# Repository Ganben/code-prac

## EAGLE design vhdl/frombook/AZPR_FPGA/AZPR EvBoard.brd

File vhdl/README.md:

## Usage
The env confirmation:
[Source: iverilog wiki](https://iverilog.fandom.com/wiki/Getting_Started)

```
% iverilog -o hello hello.v
% vvp hello
```

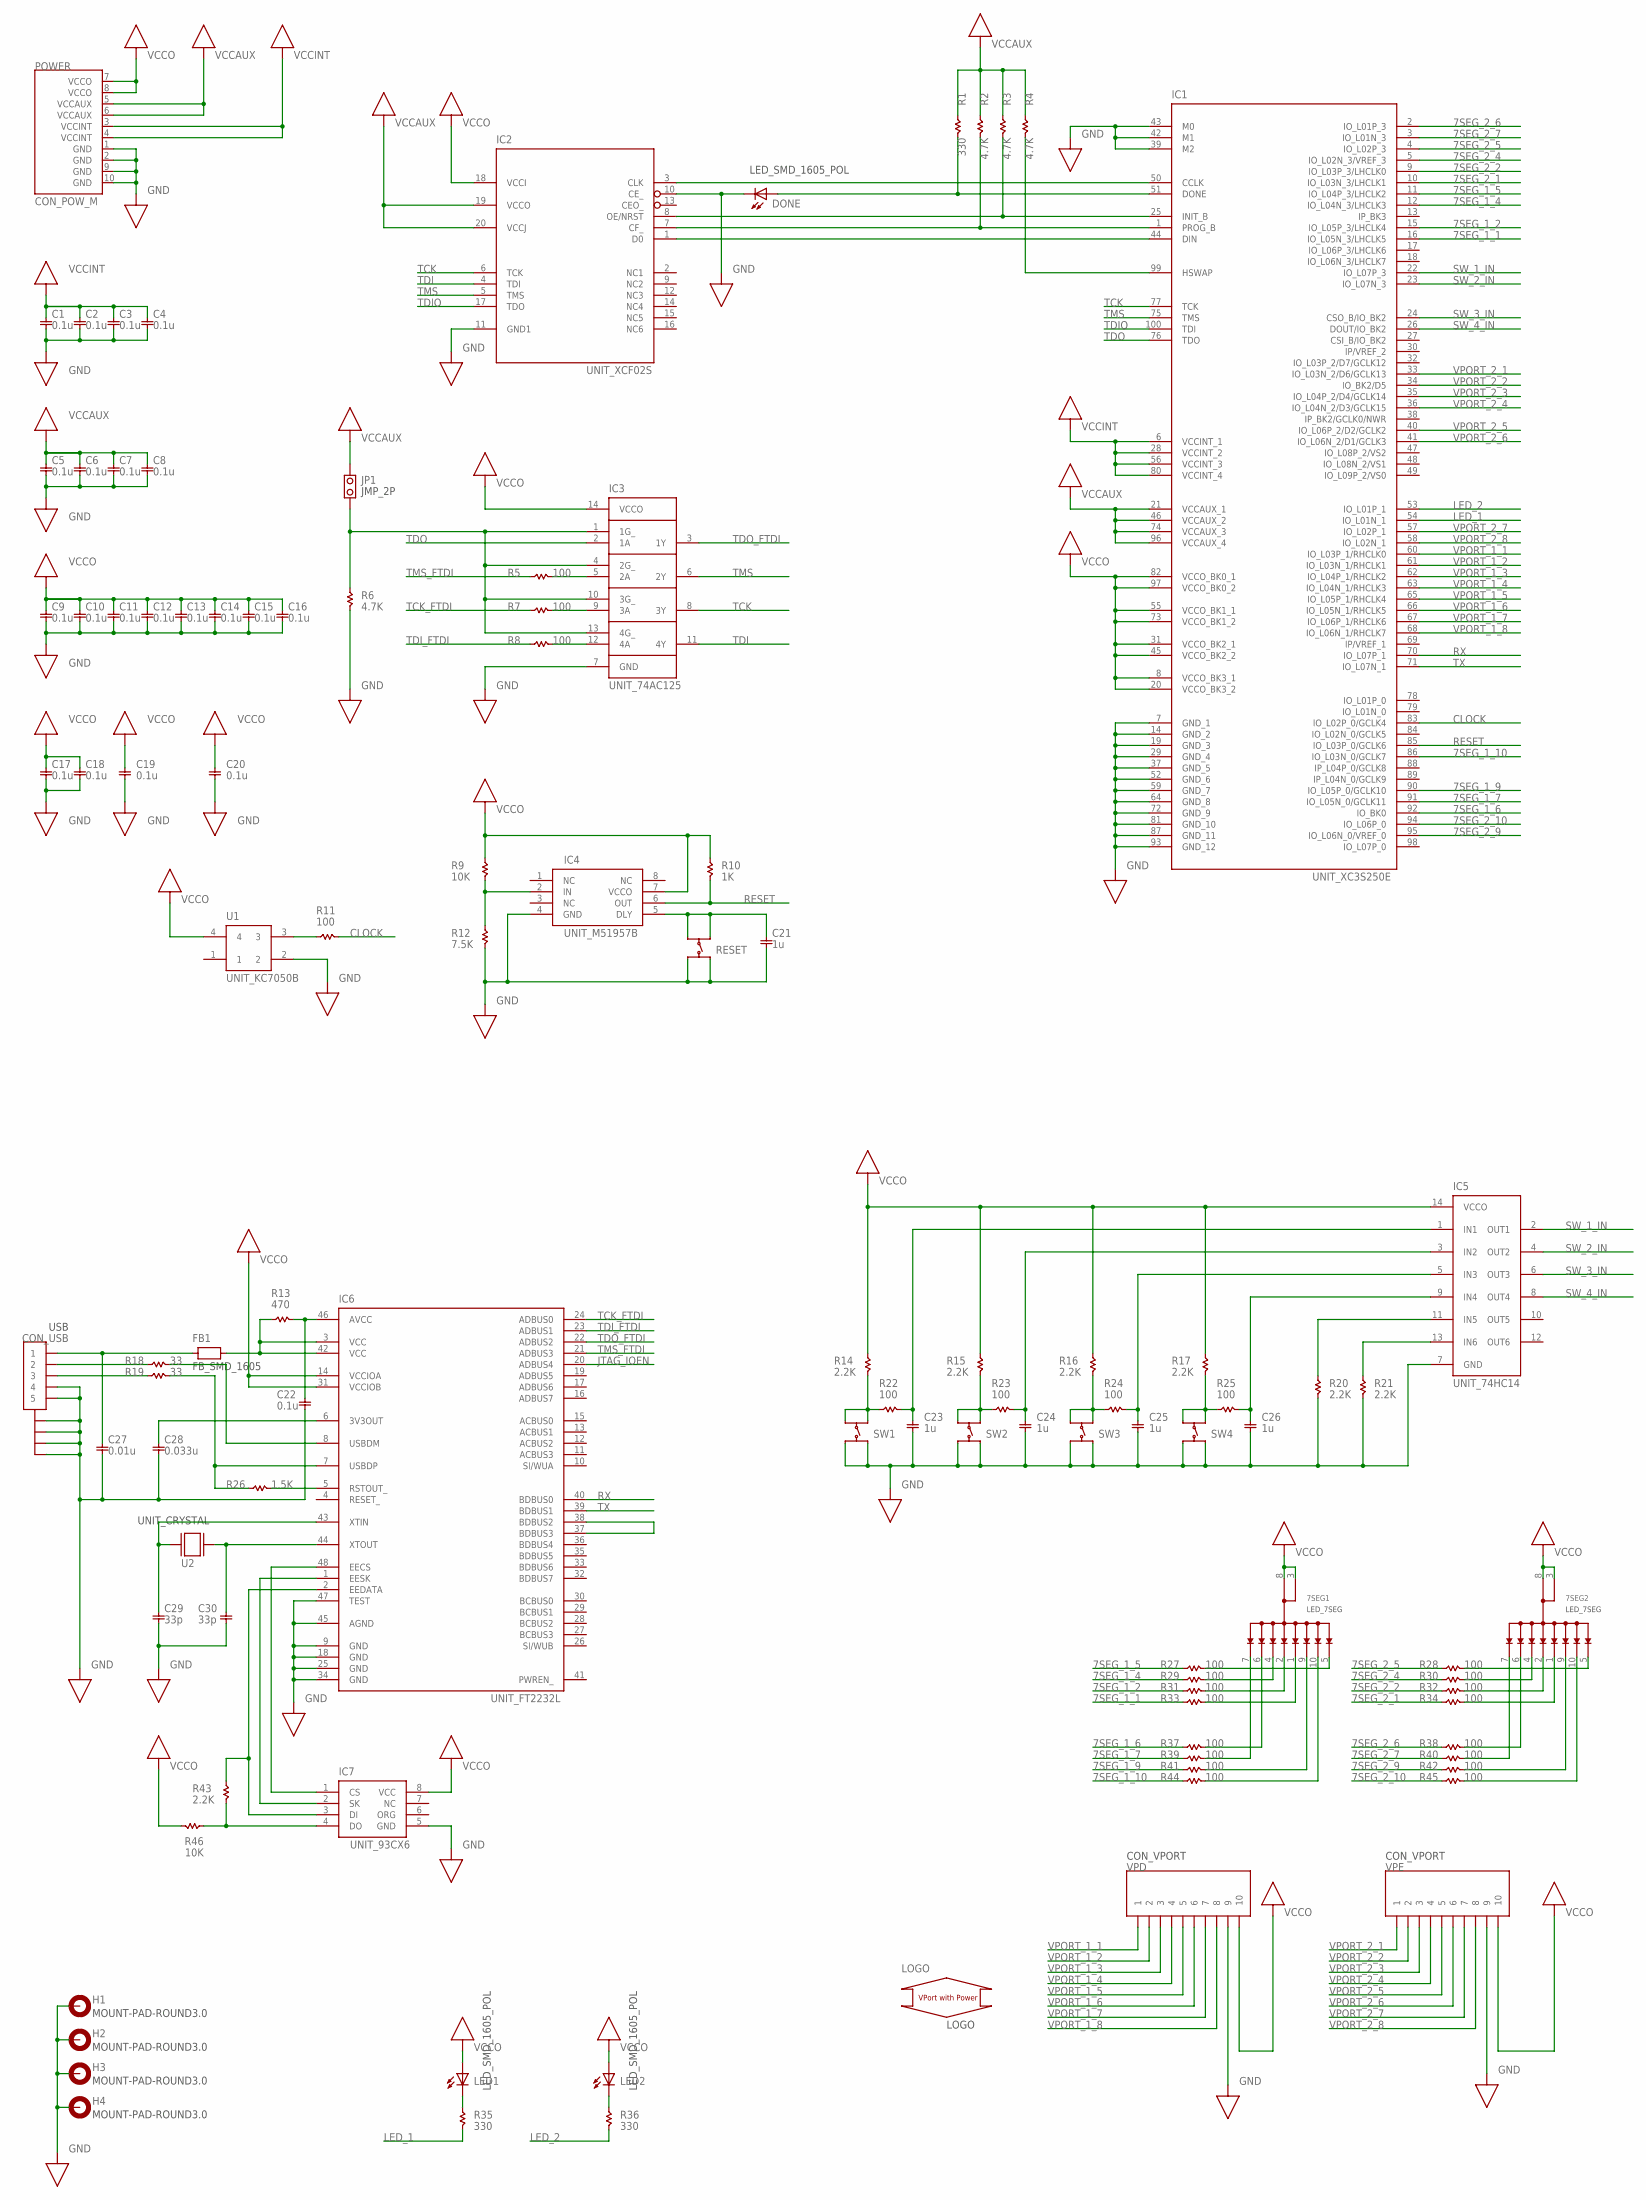
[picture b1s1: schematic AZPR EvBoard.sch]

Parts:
7SEG1, 7SEG2: LED_7SEG; SMD_LED_7SEG
C1, C2, C3, C4: 0.1u; SMDPAD_1605_04INCH
C5, C6, C7, C8: 0.1u; SMDPAD_1605_03INCH
C9, C10, C11, C12, C13, C14, C15, C16, C17: 0.1u; SMDPAD_1605_02INCH
C18, C19, C20, C22: 0.1u; SMD_1605
C21, C23, C24, C25, C26: 1u; SMD_1605
C27: 0.01u; SMD_1605
C28: 0.033u; SMD_1605
C29, C30: 33p; SMD_1605
DONE: LED_SMD_1605_POL; SMD_1605_POL
FB1: FB_SMD_1605; SMD_1605
H1, H2, H3, H4: MOUNT-PAD-ROUND3.0; HOLE_32
IC1: UNIT_XC3S250E; SMD_VQ100
IC2: UNIT_XCF02S; SMD_VO20C
IC3: UNIT_74AC125; SMD_SOP14
IC4: UNIT_M51957B; SMD_SOP8
IC5: UNIT_74HC14; SMD_SOP14
IC6: UNIT_FT2232L; SMD_LQFP48
IC7: UNIT_93CX6; SMD_SOP8
JP1: JMP_2P; PAD_JMP_2P
LED1, LED2: LED_SMD_1605_POL; SMD_1605_POL
LOGO: LOGO
POWER: CON_POW_M; PAD_POW_M
R1, R35, R36: 330; SMD_1605_R
R2, R3, R4, R6: 4.7K; SMD_1605_R
R5, R7, R8, R11, R22, R23, R24, R25, R27, R28, R29, R30, R31, R32, R33, R34, R37, R38, R39, R40, R41, R42, R44, R45: 100; SMD_1605_R
R9, R46: 10K; SMD_1605_R
R10: 1K; SMD_1605_R
R12: 7.5K; SMD_1605_R
R13: 470; SMD_1605_R
R14, R15, R16, R17, R20, R21, R43: 2.2K; SMD_1605_R
R18, R19: 33; SMD_1605_R
R26: 1.5K; SMD_1605_R
RESET: SW_PUSH; SMD_SW_PUSH
SW1, SW2, SW3, SW4: SW_PUSH; SMD_SW_PUSH
U1: UNIT_KC7050B; SMD_KC7050B
U2: UNIT_CRYSTAL; SMD_HC-49_S
USB: CON_USB; SMD_USB
VPD: CON_VPORT; PAD_VPORT
VPE: CON_VPORT; PAD_VPORT

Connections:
7SEG_1_1: IC1.16 (IO_L05N_3/LHCLK5), R33.1
7SEG_1_2: IC1.15 (IO_L05P_3/LHCLK4), R31.1
7SEG_1_4: IC1.12 (IO_L04N_3/LHCLK3), R29.1
7SEG_1_5: IC1.11 (IO_L04P_3/LHCLK2), R27.1
7SEG_1_6: IC1.92 (IO_BK0), R37.1
7SEG_1_7: IC1.91 (IO_L05N_0/GCLK11), R39.1
7SEG_1_9: IC1.90 (IO_L05P_0/GCLK10), R41.1
7SEG_1_10: IC1.86 (IO_L03N_0/GCLK7), R44.1
7SEG_2_1: IC1.10 (IO_L03N_3/LHCLK1), R34.1
7SEG_2_2: IC1.9 (IO_L03P_3/LHCLK0), R32.1
7SEG_2_4: IC1.5 (IO_L02N_3/VREF_3), R30.1
7SEG_2_5: IC1.4 (IO_L02P_3), R28.1
7SEG_2_6: IC1.2 (IO_L01P_3), R38.1
7SEG_2_7: IC1.3 (IO_L01N_3), R40.1
7SEG_2_9: IC1.95 (IO_L06N_0/VREF_0), R42.1
7SEG_2_10: IC1.94 (IO_L06P_0), R45.1
CLOCK: IC1.83 (IO_L02P_0/GCLK4), R11.2
EECS: IC6.48 (EECS), IC7.1 (CS)
EEDATA: IC6.2 (EEDATA), IC7.3 (DI), R43.1
EESK: IC6.1 (EESK), IC7.2 (SK)
EETMP: IC7.4 (DO), R43.2, R46.1
GND: C1.P$2 (2), C2.P$2 (2), C3.P$2 (2), C4.P$2 (2), C5.P$2 (2), C6.P$2 (2), C7.P$2 (2), C8.P$2 (2), C9.P$2 (2), C10.P$2 (2), C11.P$2 (2), C12.P$2 (2), C13.P$2 (2), C14.P$2 (2), C15.P$2 (2), C16.P$2 (2), C17.P$2 (2), C18.2, C19.2, C20.2, C21.2, C22.2, C23.2, C24.2, C25.2, C26.2, C27.2, C28.2, C29.2, C30.2, DONE.C, H1.B3,2, H2.B3,2, H3.B3,2, H4.B3,2, IC1.7 (GND_1), IC1.14 (GND_2), IC1.19 (GND_3), IC1.29 (GND_4), IC1.37 (GND_5), IC1.39 (M2), IC1.42 (M1), IC1.43 (M0), IC1.52 (GND_6), IC1.59 (GND_7), IC1.64 (GND_8), IC1.72 (GND_9), IC1.81 (GND_10), IC1.87 (GND_11), IC1.93 (GND_12), IC2.10 (CE_), IC2.11 (GND1), IC3.7 (GND), IC4.4 (GND), IC5.7 (GND), IC6.9 (GND), IC6.18 (GND), IC6.25 (GND), IC6.34 (GND), IC6.45 (AGND), IC6.47 (TEST), IC7.5 (GND), POWER.1 (GND), POWER.2 (GND), POWER.9 (GND), POWER.10 (GND), R6.2, R12.2, R20.2, R21.2, RESET.3, RESET.4, SW1.3, SW1.4, SW2.3, SW2.4, SW3.3, SW3.4, SW4.3, SW4.4, U1.2, USB.4, USB.5, USB.PAD@1 (PAD1), USB.PAD@2 (PAD2), USB.PAD@3 (PAD3), USB.PAD@4 (PAD4), VPD.9, VPE.9
JTAG_CCLK: IC1.50 (CCLK), IC2.3 (CLK)
JTAG_DIN: IC1.44 (DIN), IC2.1 (D0)
JTAG_DONE: DONE.A, IC1.51 (DONE), R1.2
JTAG_HSWAP: IC1.99 (HSWAP), R4.2
JTAG_INIT_B: IC1.25 (INIT_B), IC2.8 (OE/NRST), R3.2
JTAG_IOEN: IC6.20 (ADBUS4)
JTAG_PROG_B: IC1.1 (PROG_B), IC2.7 (CF_), R2.2
LED_1: IC1.54 (IO_L01N_1), R35.2
LED_2: IC1.53 (IO_L01P_1), R36.2
unnamed: IC3.1 (1G_), IC3.4 (2G_), IC3.10 (3G_), IC3.13 (4G_), JP1.P$2, R6.1
unnamed: LED1.C, R35.1
unnamed: IC3.5 (2A), R5.2
unnamed: IC3.9 (3A), R7.2
unnamed: IC3.12 (4A), R8.2
unnamed: LED2.C, R36.1
unnamed: IC6.37 (BDBUS3), IC6.38 (BDBUS2)
unnamed: R11.1, U1.3
RESET: IC1.85 (IO_L03P_0/GCLK6), IC4.6 (OUT), R10.2
RESET_IN: IC4.2 (IN), R9.2, R12.1
RESET_SW: C21.1, IC4.5 (DLY), RESET.1, RESET.2
RX: IC1.70 (IO_L07P_1), IC6.40 (BDBUS0)
SW_1_IN: IC1.22 (IO_L07P_3), IC5.2 (OUT1)
SW_1_IN_T: C23.1, IC5.1 (IN1), R22.2
SW_1_IN_T2: R14.2, R22.1, SW1.1, SW1.2
SW_2_IN: IC1.23 (IO_L07N_3), IC5.4 (OUT2)
SW_2_IN_T: C24.1, IC5.3 (IN2), R23.2
SW_2_IN_T2: R15.2, R23.1, SW2.1, SW2.2
SW_3_IN: IC1.24 (CSO_B/IO_BK2), IC5.6 (OUT3)
SW_3_IN_T: C25.1, IC5.5 (IN3), R24.2
SW_3_IN_T2: R16.2, R24.1, SW3.1, SW3.2
SW_4_IN: IC1.26 (DOUT/IO_BK2), IC5.8 (OUT4)
SW_4_IN_T: C26.1, IC5.9 (IN4), R25.2
SW_4_IN_T2: R17.2, R25.1, SW4.1, SW4.2
SW_PD_1: IC5.11 (IN5), R20.1
SW_PD_2: IC5.13 (IN6), R21.1
TCK: IC1.77 (TCK), IC2.6 (TCK), IC3.8 (3Y)
TCK_FTDI: IC6.24 (ADBUS0), R7.1
TDI: IC2.4 (TDI), IC3.11 (4Y)
TDIO: IC1.100 (TDI), IC2.17 (TDO)
TDI_FTDI: IC6.23 (ADBUS1), R8.1
TDO: IC1.76 (TDO), IC3.2 (1A)
TDO_FTDI: IC3.3 (1Y), IC6.22 (ADBUS2)
TMS: IC1.75 (TMS), IC2.5 (TMS), IC3.6 (2Y)
TMS_FTDI: IC6.21 (ADBUS3), R5.1
TX: IC1.71 (IO_L07N_1), IC6.39 (BDBUS1)
T_7SEG_1_1: 7SEG1.1 (E), R33.2
T_7SEG_1_2: 7SEG1.2 (D), R31.2
T_7SEG_1_4: 7SEG1.4 (C), R29.2
T_7SEG_1_5: 7SEG1.5 (D.P), R27.2
T_7SEG_1_6: 7SEG1.6 (B), R37.2
T_7SEG_1_7: 7SEG1.7 (A), R39.2
T_7SEG_1_9: 7SEG1.9 (F), R41.2
T_7SEG_1_10: 7SEG1.10 (G), R44.2
T_7SEG_2_1: 7SEG2.1 (E), R34.2
T_7SEG_2_2: 7SEG2.2 (D), R32.2
T_7SEG_2_4: 7SEG2.4 (C), R30.2
T_7SEG_2_5: 7SEG2.5 (D.P), R28.2
T_7SEG_2_6: 7SEG2.6 (B), R38.2
T_7SEG_2_7: 7SEG2.7 (A), R40.2
T_7SEG_2_9: 7SEG2.9 (F), R42.2
T_7SEG_2_10: 7SEG2.10 (G), R45.2
USB_33OUT: C28.1, IC6.6 (3V3OUT)
USB_AVCC: C22.1, IC6.46 (AVCC), R13.2
USB_CON1: C27.1, FB1.1, USB.1
USB_CON2: R18.1, USB.2
USB_CON3: R19.1, USB.3
USB_DM: IC6.8 (USBDM), R18.2
USB_DP: IC6.7 (USBDP), R19.2, R26.1
USB_POW: FB1.2, IC6.3 (VCC), IC6.42 (VCC), R13.1
USB_RSTOUT_: IC6.5 (RSTOUT_), R26.2
VCCAUX: C5.P$1 (1), C6.P$1 (1), C7.P$1 (1), C8.P$1 (1), IC1.21 (VCCAUX_1), IC1.46 (VCCAUX_2), IC1.74 (VCCAUX_3), IC1.96 (VCCAUX_4), IC2.19 (VCCO), IC2.20 (VCCJ), JP1.P$1, POWER.5 (VCCAUX), POWER.6 (VCCAUX), R1.1, R2.1, R3.1, R4.1
VCCINT: C1.P$1 (1), C2.P$1 (1), C3.P$1 (1), C4.P$1 (1), IC1.6 (VCCINT_1), IC1.28 (VCCINT_2), IC1.56 (VCCINT_3), IC1.80 (VCCINT_4), POWER.3 (VCCINT), POWER.4 (VCCINT)
VCCO: 7SEG1.3 (COMMON3), 7SEG1.8 (COMMON8), 7SEG2.3 (COMMON3), 7SEG2.8 (COMMON8), C9.P$1 (1), C10.P$1 (1), C11.P$1 (1), C12.P$1 (1), C13.P$1 (1), C14.P$1 (1), C15.P$1 (1), C16.P$1 (1), C17.P$1 (1), C18.1, C19.1, C20.1, IC1.8 (VCCO_BK3_1), IC1.20 (VCCO_BK3_2), IC1.31 (VCCO_BK2_1), IC1.45 (VCCO_BK2_2), IC1.55 (VCCO_BK1_1), IC1.73 (VCCO_BK1_2), IC1.82 (VCCO_BK0_1), IC1.97 (VCCO_BK0_2), IC2.18 (VCCI), IC3.14 (VCCO), IC4.7 (VCCO), IC5.14 (VCCO), IC6.14 (VCCIOA), IC6.31 (VCCIOB), IC7.8 (VCC), LED1.A, LED2.A, POWER.7 (VCCO), POWER.8 (VCCO), R9.1, R10.1, R14.1, R15.1, R16.1, R17.1, R46.2, U1.4, VPD.10, VPE.10
VPORT_1_1: IC1.60 (IO_L03P_1/RHCLK0), VPD.1
VPORT_1_2: IC1.61 (IO_L03N_1/RHCLK1), VPD.2
VPORT_1_3: IC1.62 (IO_L04P_1/RHCLK2), VPD.3
VPORT_1_4: IC1.63 (IO_L04N_1/RHCLK3), VPD.4
VPORT_1_5: IC1.65 (IO_L05P_1/RHCLK4), VPD.5
VPORT_1_6: IC1.66 (IO_L05N_1/RHCLK5), VPD.6
VPORT_1_7: IC1.67 (IO_L06P_1/RHCLK6), VPD.7
VPORT_1_8: IC1.68 (IO_L06N_1/RHCLK7), VPD.8
VPORT_2_1: IC1.33 (IO_L03N_2/D6/GCLK13), VPE.1
VPORT_2_2: IC1.34 (IO_BK2/D5), VPE.2
VPORT_2_3: IC1.35 (IO_L04P_2/D4/GCLK14), VPE.3
VPORT_2_4: IC1.36 (IO_L04N_2/D3/GCLK15), VPE.4
VPORT_2_5: IC1.40 (IO_L06P_2/D2/GCLK2), VPE.5
VPORT_2_6: IC1.41 (IO_L06N_2/D1/GCLK3), VPE.6
VPORT_2_7: IC1.57 (IO_L02P_1), VPE.7
VPORT_2_8: IC1.58 (IO_L02N_1), VPE.8
XTIN: C29.1, IC6.43 (XTIN), U2.P$1
XTOUT: C30.1, IC6.44 (XTOUT), U2.P$2

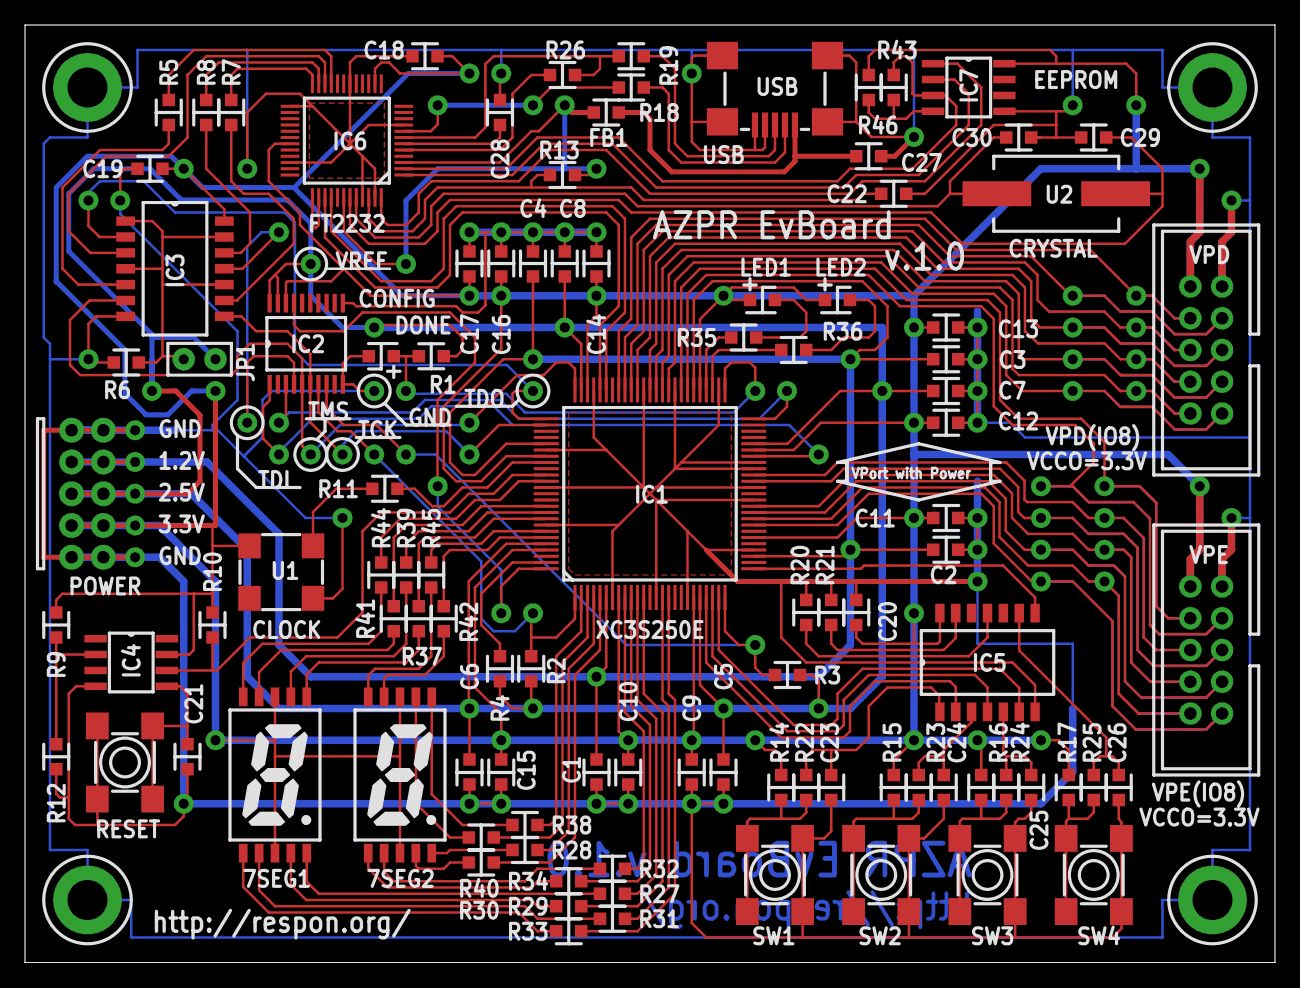
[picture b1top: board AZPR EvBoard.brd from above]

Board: 2 copper layers, 100.0 x 75.0 mm, 106 parts (0 on the bottom side), 112 nets.

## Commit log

2019-08-22 add paddle env description
2019-09-10 bump vhdl
2019-09-11 bump .v
2019-09-12 bump rust
2019-09-16 rust io /py transformer bump
2019-09-16 bump paddle basic
2019-09-16 bump azpr vhdl lib
2019-09-17 bump progress bar in rust
2019-09-18 bump pytorch examples
2019-09-19 bump pytorch nlp examples
2019-09-20 bump nn gen model rust test
2019-09-25 bump n-gram text classi
2019-09-26 bump fix last text classifier
2019-09-26 bump with nn model save/load func
2019-09-27 bump chatbot with err
2020-02-09 bump clisp
2020-02-10 bump lisp
2020-02-11 bump reduce etc
2020-02-12 go prac
2020-02-13 bump circular buffer
2020-02-14 bump cocktailsort
2020-02-15 bump combsort and part DLinkList
2020-02-16 bump ExpSearch
2020-02-17 bump go - gnome sort
2020-02-18 bump js linkedlist go hashtable
2020-02-19 bump linked list js
2020-02-19 bump insertion sort
2020-02-20 bump go test n js hashtable
2020-02-21 bump b tree node js
2020-02-22 bump go jump search, bin search tree
2020-02-22 bump ebnf compiles
2020-02-23 bump 1/2 red-black-tree js
2020-02-23 bump go test faul
2020-02-24 bump mergesort go, red-black-tree js
2020-02-25 daily bump py test ward, js stack, go string search
2020-02-26 bump rabinkarp go
2020-02-28 bump reversearray and rabinkarp go
2020-02-29 bump trie node
2020-03-01 bump trie js, selectionsort go
2020-03-03 bump heap js
2020-03-04 bump stack go, max min heap js
2020-03-05 bump 2
2020-03-06 bump trie go
2020-03-09 bump linkedlist traversal
2020-03-10 bump js algo math 2
2020-03-12 bump js factorial
2020-03-13 bump go leet1
2020-03-14 bump go leet 2
2020-03-15 bump go leet 3,4
2020-03-16 bump longest parlin substr
2020-03-17 bump zigzag go leet
2020-03-18 bump go leet 8
2020-03-19 bump go leet re match
2020-03-20 bump go leet maxarea
2020-03-21 bump go leet 14
2020-03-22 bump go leet 16
2020-03-23 bump go leet 18
2020-03-24 bump go leet 20
2020-03-25 bump 23 go leet
2020-03-26 go leet 24
2020-03-27 bump go leet 25
2020-03-28 bump go leet 28
2020-03-29 bump go leet 30
2020-03-30 bump go leet 32
2020-03-31 bump go leet 34
2020-04-01 bump go leet 36
2020-04-02 bump go leet 37
2020-04-03 bump go leet 39
2020-04-04 bump go leet 41
2020-04-05 bump go leet 42
2020-04-06 bump gorgonia, go leet 44
2020-04-07 bump go leet 46
2020-04-08 bump go leet 47 commited
2020-04-09 bump go leet 48 pass
2020-04-10 bump leet 49 go
2020-04-11 bump go leet 50 and dp
2020-04-12 bump go n queen
2020-04-12 bump go nqueen 2
2020-04-13 go leet 53 dp
2020-04-14 bump go leet 54
2020-04-15 bump go leet 56 with mergesort
2020-04-16 bump go leet 57
2020-04-17 bump osdev, leet go 59
2020-04-18 bump leet 60
2020-04-19 bump leet 61
2020-04-20 bump go leet 200
2020-04-21 bump go leet 63
2020-04-22 go leet 64
2020-04-23 bump go leet 65
2020-04-26 bump mergeKlist
2020-04-28 bump leet daily
2020-04-29 bump 1095
2020-04-30 bump 202
2020-05-02 bump 68 dnf
2020-05-03 bump 69
2020-05-04 bump 70
2020-05-05 bump 71
2020-05-06 bump 72
2020-05-07 bump daily
2020-05-08 bump 73
2020-05-09 bump 75
2020-05-10 bump 76
2020-05-20 bump x
2020-05-21 bump 80
2020-05-22 bump 105
2020-05-24 bump wordsearch full
2020-05-25 bump 145
2020-05-26 bump 81
2020-05-30 bump 83
2020-05-31 bump 84
2020-06-02 attempt ..
2020-06-03 bump new21
2020-06-05 bump something
2020-06-07 bump
2020-06-10 bump 88
2020-06-11 bump 90
2020-06-12 bump92
2020-06-14 bump 95
2020-06-15 bump 100
2020-06-16 bump 102
2020-06-17 bump 103
2020-06-20 bump 107
2020-06-21 bump 106
2020-06-22 bump 114
2020-06-24 bump 116
2020-06-27 bump 117
2020-06-28 bump 119
2020-06-29 bump 121
2020-06-30 bump 124
2020-07-01 bump 127
2020-07-02 bump 128
2020-07-03 bump 131
2020-07-04 bump 132
2020-07-05 bump 134
2020-07-07 bump 136
2020-07-08 bump 138
2020-07-09 bump 140
2020-07-10 bump 142
2020-07-11 bump 144
2020-07-13 bump h 149
2020-07-14 bump 150
2020-07-15 bump 152
2020-07-17 b 154
2020-07-18 bump 160
2020-07-20 bump 167
2020-07-23 bum 168
2020-07-25 bump 171
2020-07-26 bump 172
2020-07-27 bump 173
2020-08-01 bump 178
2020-08-02 bump 180
2020-08-03 bump 182
2020-08-05 bump 187
2020-08-06 bump 189
2020-08-07 bump 191
2020-08-08 bump 196
2020-08-09 bump 198
2020-08-12 bump 203
2020-08-15 bump 205
2020-08-17 bump 210
2020-08-19 bump 211
2020-08-20 bump 213
2020-08-21 bump 217
2020-08-22 bump 220
2020-08-24 bump 223
2020-08-25 bump 226
2020-08-26 bump 227
2020-08-27 bump 229
2020-08-29 bump 231
2020-08-30 bump 233
2020-08-31 bump name search
2020-09-01 bump name char dict
2020-09-02 bump 237
2020-09-05 bump 239
2020-09-06 bump contest205
2020-09-07 bump 241
2020-09-16 bump 267
2020-10-13 b263
2020-10-14 b264
2020-10-15 b273
2020-10-18 b274
2020-10-19 b275
2020-10-20 b279
2020-10-21 b282
2020-10-22 b289
2020-10-23 bump284
2020-10-24 b293
2020-10-27 b299
2020-11-18 bump 304
2020-11-19 bump 306
2020-11-20 bump 310
2020-11-21 bump 310 unsolved
2020-11-22 bump 313
2020-11-23 min arrow
2020-11-24 bump 222,316
2020-11-25 bump 318
2020-11-26 bump 321
2020-11-29 failed 322
2020-11-30 bump 767
2020-12-01 dnf 324
2020-12-02 bump 326
2020-12-03 bump 324
2020-12-06 bump 330
2020-12-06 bump 324 fail
2020-12-20 bump 331
2020-12-22 bump 334
2020-12-23 bump 335
2020-12-24 bump 338
2020-12-27 bump 342
2020-12-28 bump 343
2020-12-29 bump 345
2021-01-01 bump 348
2021-01-06 partial fullfil 352
2021-01-07 bump 300
2021-01-08 bump 354
2021-01-09 bump 357
2021-01-11 bump 1202
2021-01-12 bump 365
2021-01-12 bump 1203
2021-01-13 bump 367
2021-01-17 bump 368
2021-01-18 bump 371
2021-01-19 bump 372
2021-01-20 bump373
2021-01-21 bump 373
2021-01-22 bump 375
2021-01-23 bump 376
2021-01-25 bump 380
2021-01-26 bump 381, total 302
2021-01-30 bump 383
2021-01-31 bump weekly contest
2021-02-01 bump 384
2021-02-02 bump 385
2021-02-03 bump 386
2021-02-04 bump 388
2021-02-06 bump 390
2021-02-07 bump 391
2021-02-08 bump 393
2021-02-09 bump 394
2021-02-10 bump 395
2021-02-11 topK
2021-02-13 bump 397
2021-02-14 bump 398
2021-02-15 bump 399
2021-02-16 bump 400
2021-02-17 bump 401
2021-02-19 bump 402
2021-02-25 bump 403
2021-02-26 bump 404
2021-02-28 bump 405
2021-03-02 bump 406
2021-03-03 bump 407
2021-03-08 bump 409
2021-03-15 bump 412
2021-03-16 bump 413
2021-03-17 bump 414
2021-03-24 bump 416
2021-03-26 bump 419
2021-03-30 bump 420
2021-03-31 bump 421
2021-04-01 bump 423
2021-04-02 bump 429
2021-04-04 bump 430
2021-04-13 bump 433
2021-04-20 bump 434
2021-04-23 bump 435
2021-04-24 bump 436
2021-04-25 bump 437
2021-04-26 bump 438
2021-04-27 bump 441
2021-04-28 bump 442
2021-04-29 bump 443
2021-04-30 bump 445
2021-05-01 bump 447
2021-05-03 bump 450
2021-05-10 bump 872
2021-05-12 bump 453
2021-05-17 bump 451
2021-05-18 daily bump
2021-05-26 bump 455
2021-05-27 bump 456
2021-05-28 bump 457
2021-06-14 bump 458
2021-06-16 bump 877
2021-06-18 bump 483
2021-06-19 bump 1239
2021-06-21 bump 462
2021-06-24 bump 149
2021-06-28 bump 815
2021-07-25 bump 463
2021-07-29 bump 464
2021-08-01 bump 467
2021-08-02 bump 468
2021-08-07 bump 470)
2021-08-08 b 472
2021-08-10 b 474
2021-08-11 b 475
2021-08-13 b 476
2021-08-19 bump 478
2021-08-23 bump 479
2021-08-25 bump d
2021-08-28 bump d: ?
2021-08-30 bump 482
2021-09-05 bump 486
2021-09-06 bump 488
2021-09-07 daily
2021-09-08 bump 489
2021-09-09 bump 492
2021-09-10 bump 493
2021-09-11 bump 495
2021-09-13 bump 496
2021-09-15 bump 497
2021-09-18 bump 498
2021-09-23 bump 500
2021-10-03 bump 503
2021-10-05 bump 504
2021-11-18 bump 563
2021-11-19 bump 506
2021-11-21 bump 559
2021-11-22 bump 507
2021-11-23 bump 895
2021-11-24 bump 508
2021-11-25 bump 700
2021-11-27 bump 519
2021-11-30 bump 509
2021-12-06 bump 1816
2021-12-10 bump 748
2021-12-11 bump 911
2021-12-12 bump 709
2021-12-13 bump 807
2021-12-20 bump 513
2021-12-21 bump 1154
2021-12-22 bump 686
2021-12-24 bump 1705
2021-12-25 bump 1609
2021-12-29 bump 1995
2021-12-31 bump 514
2022-01-01 b 2022
2022-01-03 b 515
2022-01-04 b 913
2022-01-05 b 1576
2022-01-07 b 1614
2022-01-13 b 747
2022-01-14 b 516
2022-01-15 b 517
